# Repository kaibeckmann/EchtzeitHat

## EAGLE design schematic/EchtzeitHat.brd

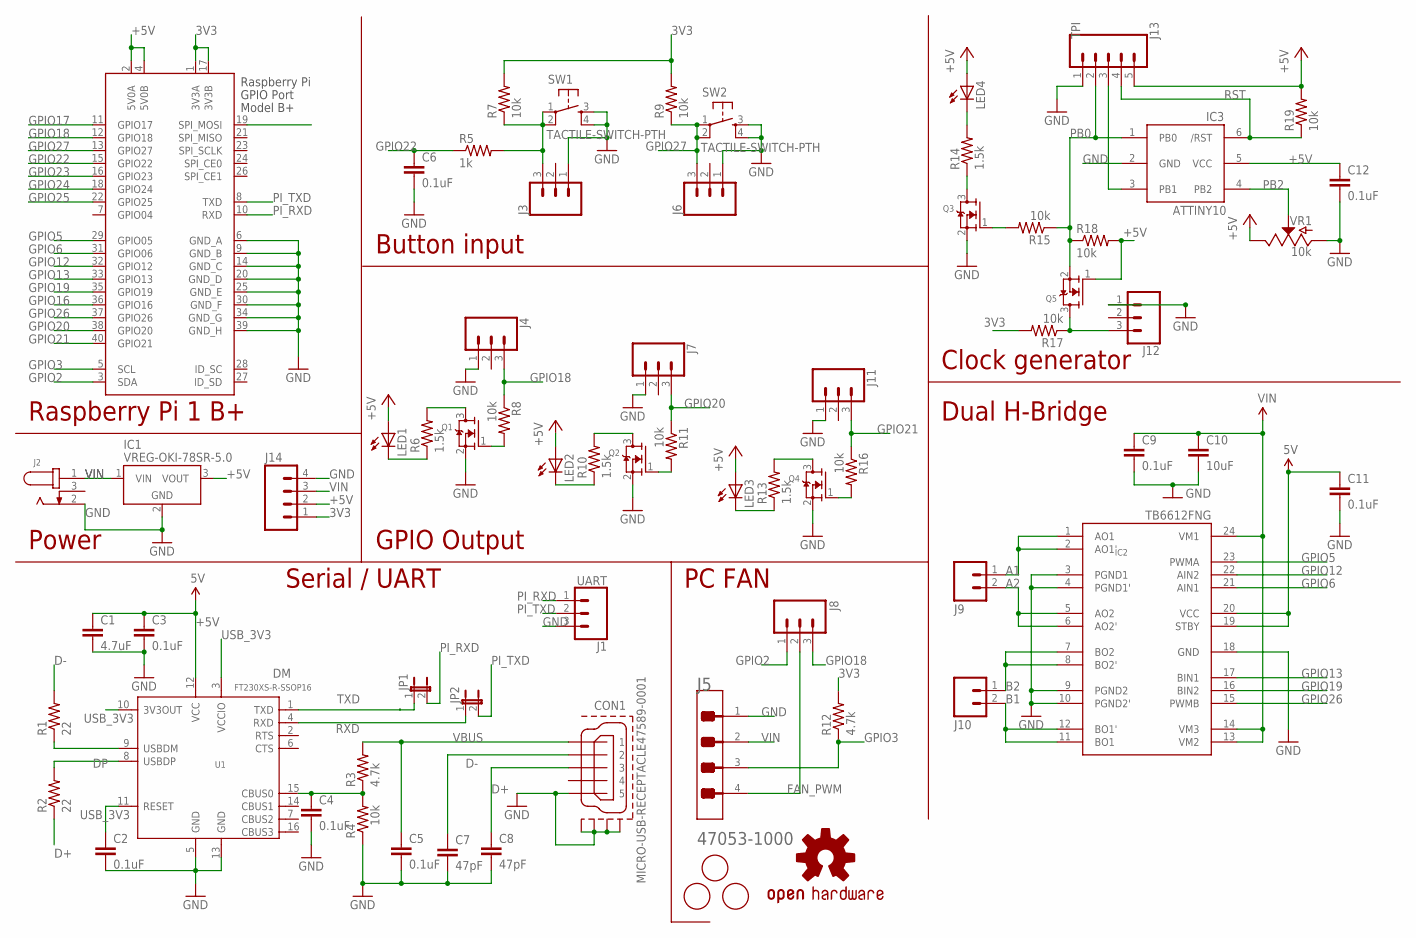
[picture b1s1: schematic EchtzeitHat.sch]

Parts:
C1: 4.7uF; 0805-CAP
C2, C3, C4, C5, C6, C9, C11, C12: 0.1uF; 0805-CAP
C7, C8: 47pF; 0805-CAP
C10: 10uF; 0805-CAP
CON1: MICRO-USB-RECEPTACLE47589-0001; 47589-0001
FI1, FI2, FI3: FIDUCIAL; FIDUCIAL_1MM
IC1: VREG-OKI-78SR-5.0; OKI-78SR-H
IC2: TB6612FNG; SSOP24
IC3: ATTINY10; SOT23-6
J1: UART; 1X03_LOCK
J2: PJ-102A; CUI_PJ-102A
J3, J4, J6, J7, J11, J12: CONN_03LOCK; 1X03_LOCK
J5: MOLEX_47053-1000MOLEX_47053-1000_0_0; MOLEX_47053-1000_0
J8: M03LOCK; 1X03_LOCK
J9, J10: M023.5MM_LOCK; SCREWTERMINAL-3.5MM-2_LOCK
J13: TPI; 1X05_LOCK
J14: M04LOCK; 1X04_LOCK
JP1, JP2: JUMPER-2SMD-NC; SJ_2S
LED1, LED2, LED3, LED4: LEDCHIPLED_0805; CHIPLED_0805
LOGO1: OSHW-LOGOL; OSHW-LOGO-L
Q1, Q2, Q3, Q4, Q5: MOSFET-NREFLOW; SOT23
R1, R2: 22; 0805
R3, R12: 4.7k; 0805
R4, R7, R8, R9, R11, R15, R16, R17, R18, R19: 10k; 0805
R5: 1k; 0805
R6, R10, R13, R14: 1.5k; 0805
SW1, SW2: TACTILE-SWITCH-PTH; TAC-SWITCH-PTH
U1: FT230XS-R-SSOP16; SSOP16-0.635-5X4MM
VR1: 10k; POT-PTH-ALPS-KIT
X1: RASPI_BOARD_B+#_H; RASPI_BOARD_B+HAT

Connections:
3V3: J14.1, R7.2, R9.2, R12.2, R17.2, X1.1 (3V3A), X1.17 (3V3B)
+5V: C1.1, C3.1, C11.1, C12.1, IC1.3 (VOUT), IC2.19 (STBY), IC2.20 (VCC), IC3.5 (VCC), J13.5, J14.2, LED1.A, LED2.A, LED3.A, LED4.A, Q5.1 (G), R18.2, R19.2, U1.12 (VCC), VR1.P$1 (E), X1.2 (5V0A), X1.4 (5V0B)
A1: IC2.1 (AO1), IC2.2 (AO1'), J9.1
A2: IC2.5 (AO2), IC2.6 (AO2'), J9.2
B1: IC2.11 (BO1), IC2.12 (BO1'), J10.2
B2: IC2.7 (BO2), IC2.8 (BO2'), J10.1
CBUS: C4.1, R3.1, R4.2, U1.15 (CBUS0)
D+: C8.1, CON1.3, R2.1
D-: C7.1, CON1.2, R1.2
DM: R1.1, U1.9 (USBDM)
DP: R2.2, U1.8 (USBDP)
FAN_PWM: J5.4, J8.2
GND: C1.2, C2.2, C3.2, C4.2, C5.2, C6.2, C7.2, C8.2, C9.2, C10.2, C11.2, C12.2, CON1.5, CON1.CASING1 (GND1), CON1.CASING2 (GND2), CON1.CASING3 (GND3), CON1.CASING4 (GND4), IC1.2 (GND), IC2.3 (PGND1), IC2.4 (PGND1'), IC2.9 (PGND2), IC2.10 (PGND2'), IC2.18 (GND), IC3.2 (GND), J1.3, J2.2, J3.1, J4.1, J5.1, J6.1, J7.1, J11.1, J12.1, J13.1, J14.4, Q1.2 (S), Q2.2 (S), Q3.2 (S), Q4.2 (S), R4.1, SW1.3, SW1.4, SW2.3, SW2.4, U1.5 (GND), U1.13 (GND), VR1.P$3 (A), X1.6 (GND_A), X1.9 (GND_B), X1.14 (GND_C), X1.20 (GND_D), X1.25 (GND_E), X1.30 (GND_F), X1.34 (GND_G), X1.39 (GND_H)
GPIO2: J8.1, X1.3 (SDA)
GPIO3: J5.3, R12.1, X1.5 (SCL)
GPIO5: IC2.23 (PWMA), X1.29 (GPIO05)
GPIO6: IC2.21 (AIN1), X1.31 (GPIO06)
GPIO12: IC2.22 (AIN2), X1.32 (GPIO12)
GPIO13: IC2.17 (BIN1), X1.33 (GPIO13)
GPIO16: X1.36 (GPIO16)
GPIO17: X1.11 (GPIO17)
GPIO18: J4.3, J8.3, R8.1, X1.12 (GPIO18)
GPIO19: IC2.16 (BIN2), X1.35 (GPIO19)
GPIO20: J7.3, R11.1, X1.38 (GPIO20)
GPIO21: J11.3, R16.1, X1.40 (GPIO21)
GPIO22: C6.1, R5.1, X1.15 (GPIO22)
GPIO23: X1.16 (GPIO23)
GPIO24: X1.18 (GPIO24)
GPIO25: X1.22 (GPIO25)
GPIO26: IC2.15 (PWMB), X1.37 (GPIO26)
GPIO27: J6.3, R9.1, SW2.1, SW2.2, X1.13 (GPIO27)
unnamed: LED1.C, R6.1
unnamed: IC3.3 (PB1), J13.3
unnamed: Q1.3 (D), R6.2
unnamed: Q1.1 (G), R8.2
unnamed: LED4.C, R14.2
unnamed: Q3.3 (D), R14.1
unnamed: Q3.1 (G), R15.2
unnamed: J3.3, R5.2, R7.1, SW1.1, SW1.2
unnamed: LED2.C, R10.1
unnamed: Q2.3 (D), R10.2
unnamed: Q2.1 (G), R11.2
unnamed: LED3.C, R13.1
unnamed: Q4.3 (D), R13.2
unnamed: Q4.1 (G), R16.2
OSC: J12.3, Q5.3 (D), R17.1
PB0: IC3.1 (PB0), J13.2, Q5.2 (S), R15.1, R18.1
PB2: IC3.4 (PB2), VR1.P$2 (S)
PI_RXD: J1.1, JP1.2, X1.10 (RXD)
PI_TXD: J1.2, JP2.2, X1.8 (TXD)
RST: IC3.6 (/RST), J13.4, R19.1
RXD: JP2.1, U1.4 (RXD)
TXD: JP1.1, U1.1 (TXD)
USB_3V3: C2.1, U1.3 (VCCIO), U1.10 (3V3OUT), U1.11 (RESET)
VBUS: C5.1, CON1.1, R3.2
VIN: C9.1, C10.1, IC1.1 (VIN), IC2.13 (VM2), IC2.14 (VM3), IC2.24 (VM1), J2.1, J5.2, J14.3

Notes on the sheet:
Serial / UART
PC FAN
Power
Raspberry Pi 1 B+
Dual H-Bridge
Clock generator
Button input
GPIO Output

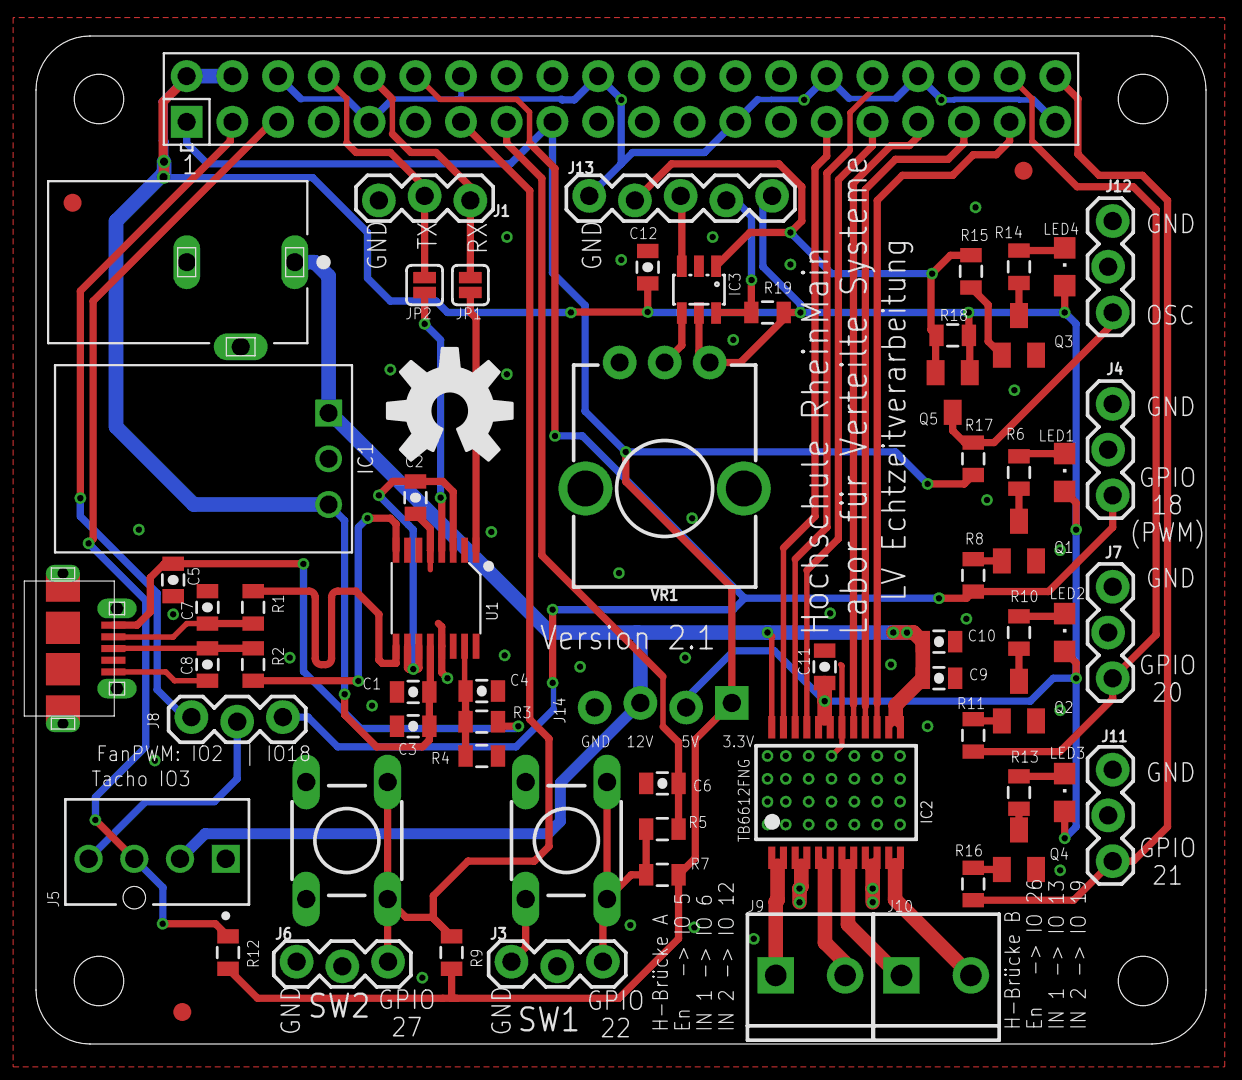
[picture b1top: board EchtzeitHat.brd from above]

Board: 2 copper layers, 65.0 x 56.0 mm, 69 parts (1 on the bottom side), 51 nets.

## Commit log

2020-04-17 version 2.1 of the EchtzeitHat

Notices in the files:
parts and their libraries:
SparkFun-Resistors: Licensing: Creative Commons ShareAlike 4.0 International - https://creativecommons.org/licenses/by-sa/4.0
con-molex-usb: (C) 2014 Tomasz Boleslaw CEDRO, cederom@tlen.pl, http://www.tomek.cedro.info.
